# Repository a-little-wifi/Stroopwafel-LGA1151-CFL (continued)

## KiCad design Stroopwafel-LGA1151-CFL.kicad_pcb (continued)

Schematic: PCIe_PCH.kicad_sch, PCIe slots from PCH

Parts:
C69, C70, C71, C72, C73, C74, C75, C76, C77, C78, C79, C80, C81, C82, C83, C84, C85, C86, C87, C88, C89, C90, C91, C92, C93, C94, C95, C96, C97, C98, C99, C100, C101, C102, C103, C104, C105, C106, C107, C108: 0.22uF; C_0402_1005Metric
J6: Bus_M.2_Socket_M; m-key
J7: PCIe_x4_PCH_6; PCIe_x4_tht_open
J10: PCIe_x4_PCH_5; PCIe_x4_tht_open
J11: PCIe_x4_PCH_4; PCIe_x4_tht_open
J12: PCIe_x4_PCH_1; PCIe_x4_tht_open

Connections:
/PCIe_PCH/PCH_x4_1_PCIe_C_Tx0+: C101.2, J12.B14 (PETp0)
/PCIe_PCH/PCH_x4_1_PCIe_C_Tx0-: C102.2, J12.B15 (PETn0)
/PCIe_PCH/PCH_x4_1_PCIe_C_Tx1+: C103.2, J12.B19 (PETp1)
/PCIe_PCH/PCH_x4_1_PCIe_C_Tx1-: C104.2, J12.B20 (PETn1)
/PCIe_PCH/PCH_x4_1_PCIe_C_Tx2+: C105.2, J12.B23 (PETp2)
/PCIe_PCH/PCH_x4_1_PCIe_C_Tx2-: C106.2, J12.B24 (PETn2)
/PCIe_PCH/PCH_x4_1_PCIe_C_Tx3+: C107.2, J12.B27 (PETp3)
/PCIe_PCH/PCH_x4_1_PCIe_C_Tx3-: C108.2, J12.B28 (PETn3)
/PCIe_PCH/PCH_x4_4_PCIe_C_Tx0+: C93.2, J11.B14 (PETp0)
/PCIe_PCH/PCH_x4_4_PCIe_C_Tx0-: C94.2, J11.B15 (PETn0)
/PCIe_PCH/PCH_x4_4_PCIe_C_Tx1+: C95.2, J11.B19 (PETp1)
/PCIe_PCH/PCH_x4_4_PCIe_C_Tx1-: C96.2, J11.B20 (PETn1)
/PCIe_PCH/PCH_x4_4_PCIe_C_Tx2+: C97.2, J11.B23 (PETp2)
/PCIe_PCH/PCH_x4_4_PCIe_C_Tx2-: C98.2, J11.B24 (PETn2)
/PCIe_PCH/PCH_x4_4_PCIe_C_Tx3+: C99.2, J11.B27 (PETp3)
/PCIe_PCH/PCH_x4_4_PCIe_C_Tx3-: C100.2, J11.B28 (PETn3)
/PCIe_PCH/PCH_x4_5_PCIe_C_Tx0+: C85.2, J10.B14 (PETp0)
/PCIe_PCH/PCH_x4_5_PCIe_C_Tx0-: C86.2, J10.B15 (PETn0)
/PCIe_PCH/PCH_x4_5_PCIe_C_Tx1+: C87.2, J10.B19 (PETp1)
/PCIe_PCH/PCH_x4_5_PCIe_C_Tx1-: C88.2, J10.B20 (PETn1)
/PCIe_PCH/PCH_x4_5_PCIe_C_Tx2+: C89.2, J10.B23 (PETp2)
/PCIe_PCH/PCH_x4_5_PCIe_C_Tx2-: C90.2, J10.B24 (PETn2)
/PCIe_PCH/PCH_x4_5_PCIe_C_Tx3+: C91.2, J10.B27 (PETp3)
/PCIe_PCH/PCH_x4_5_PCIe_C_Tx3-: C92.2, J10.B28 (PETn3)
/PCIe_PCH/PCH_x4_6_PCIe_C_Tx0+: C77.2, J7.B14 (PETp0)
/PCIe_PCH/PCH_x4_6_PCIe_C_Tx0-: C78.2, J7.B15 (PETn0)
/PCIe_PCH/PCH_x4_6_PCIe_C_Tx1+: C79.2, J7.B19 (PETp1)
/PCIe_PCH/PCH_x4_6_PCIe_C_Tx1-: C80.2, J7.B20 (PETn1)
/PCIe_PCH/PCH_x4_6_PCIe_C_Tx2+: C81.2, J7.B23 (PETp2)
/PCIe_PCH/PCH_x4_6_PCIe_C_Tx2-: C82.2, J7.B24 (PETn2)
/PCIe_PCH/PCH_x4_6_PCIe_C_Tx3+: C83.2, J7.B27 (PETp3)
/PCIe_PCH/PCH_x4_6_PCIe_C_Tx3-: C84.2, J7.B28 (PETn3)
/PCIe_PCH/SSD0_PCIe_C_Tx1+: C71.2, J6.37 (PETp1)
/PCIe_PCH/SSD0_PCIe_C_Tx1-: C72.2, J6.35 (PETn1)
/PCIe_PCH/SSD0_PCIe_C_Tx2+: C73.2, J6.25 (PETp2)
/PCIe_PCH/SSD0_PCIe_C_Tx2-: C74.2, J6.23 (PETn2)
/PCIe_PCH/SSD0_PCIe_C_Tx3+: C75.2, J6.13 (PETp3)
/PCIe_PCH/SSD0_PCIe_C_Tx3-: C76.2, J6.11 (PETn3)
/PCIe_PCH/SSD0_SATA/PCIe_C_Tx0+: C69.2, J6.49 (PETp0/SATA-A+)
/PCIe_PCH/SSD0_SATA/PCIe_C_Tx0-: C70.2, J6.47 (PETn0/SATA-A-)
GND: J6.1 (GND), J6.3 (GND), J6.9 (GND), J6.15 (GND), J6.21 (GND), J6.27 (GND), J6.33 (GND), J6.39 (GND), J6.45 (GND), J6.51 (GND), J6.57 (GND), J6.71 (GND), J6.73 (GND), J6.75 (GND), J7.A1 (~PRSNT1), J10.A1 (~PRSNT1), J11.A1 (~PRSNT1), J12.A1 (~PRSNT1); also elsewhere on the board
unnamed: J7.A4 (GND), J7.A12 (GND), J7.A15 (GND), J7.A18 (GND), J7.A20 (GND), J7.A23 (GND), J7.A24 (GND), J7.A27 (GND), J7.A28 (GND), J7.A31 (GND)
unnamed: J7.B4 (GND), J7.B7 (GND), J7.B13 (GND), J7.B16 (GND), J7.B18 (GND), J7.B21 (GND), J7.B22 (GND), J7.B25 (GND), J7.B26 (GND), J7.B29 (GND), J7.B32 (GND)
unnamed: J10.A4 (GND), J10.A12 (GND), J10.A15 (GND), J10.A18 (GND), J10.A20 (GND), J10.A23 (GND), J10.A24 (GND), J10.A27 (GND), J10.A28 (GND), J10.A31 (GND)
unnamed: J10.B4 (GND), J10.B7 (GND), J10.B13 (GND), J10.B16 (GND), J10.B18 (GND), J10.B21 (GND), J10.B22 (GND), J10.B25 (GND), J10.B26 (GND), J10.B29 (GND), J10.B32 (GND)
unnamed: J11.A4 (GND), J11.A12 (GND), J11.A15 (GND), J11.A18 (GND), J11.A20 (GND), J11.A23 (GND), J11.A24 (GND), J11.A27 (GND), J11.A28 (GND), J11.A31 (GND)
unnamed: J11.B4 (GND), J11.B7 (GND), J11.B13 (GND), J11.B16 (GND), J11.B18 (GND), J11.B21 (GND), J11.B22 (GND), J11.B25 (GND), J11.B26 (GND), J11.B29 (GND), J11.B32 (GND)
unnamed: J12.A4 (GND), J12.A12 (GND), J12.A15 (GND), J12.A18 (GND), J12.A20 (GND), J12.A23 (GND), J12.A24 (GND), J12.A27 (GND), J12.A28 (GND), J12.A31 (GND)
unnamed: J12.B4 (GND), J12.B7 (GND), J12.B13 (GND), J12.B16 (GND), J12.B18 (GND), J12.B21 (GND), J12.B22 (GND), J12.B25 (GND), J12.B26 (GND), J12.B29 (GND), J12.B32 (GND)
PCH_x4_1_CLKREQ#: J12.B17 (~PRSNT2), J12.B31 (~PRSNT2); also elsewhere on the board
PCH_x4_1_PCIe_Rx0+: J12.A16 (PERp0); also elsewhere on the board
PCH_x4_1_PCIe_Rx0-: J12.A17 (PERn0); also elsewhere on the board
PCH_x4_1_PCIe_Rx1+: J12.A21 (PERp1); also elsewhere on the board
PCH_x4_1_PCIe_Rx1-: J12.A22 (PERn1); also elsewhere on the board
PCH_x4_1_PCIe_Rx2+: J12.A25 (PERp2); also elsewhere on the board
PCH_x4_1_PCIe_Rx2-: J12.A26 (PERn2); also elsewhere on the board
PCH_x4_1_PCIe_Rx3+: J12.A29 (PERp3); also elsewhere on the board
PCH_x4_1_PCIe_Rx3-: J12.A30 (PERn3); also elsewhere on the board
PCH_x4_1_PCIe_Tx0+: C101.1; also elsewhere on the board
PCH_x4_1_PCIe_Tx0-: C102.1; also elsewhere on the board
PCH_x4_1_PCIe_Tx1+: C103.1; also elsewhere on the board
PCH_x4_1_PCIe_Tx1-: C104.1; also elsewhere on the board
PCH_x4_1_PCIe_Tx2+: C105.1; also elsewhere on the board
PCH_x4_1_PCIe_Tx2-: C106.1; also elsewhere on the board
PCH_x4_1_PCIe_Tx3+: C107.1; also elsewhere on the board
PCH_x4_1_PCIe_Tx3-: C108.1; also elsewhere on the board
PCH_x4_1_Refclk+: J12.A13 (REFCLK+); also elsewhere on the board
PCH_x4_1_Refclk-: J12.A14 (REFCLK-); also elsewhere on the board
PCH_x4_4_CLKREQ#: J11.B17 (~PRSNT2), J11.B31 (~PRSNT2); also elsewhere on the board
PCH_x4_4_PCIe_Rx0+: J11.A16 (PERp0); also elsewhere on the board
PCH_x4_4_PCIe_Rx0-: J11.A17 (PERn0); also elsewhere on the board
PCH_x4_4_PCIe_Rx1+: J11.A21 (PERp1); also elsewhere on the board
PCH_x4_4_PCIe_Rx1-: J11.A22 (PERn1); also elsewhere on the board
PCH_x4_4_PCIe_Rx2+: J11.A25 (PERp2); also elsewhere on the board
PCH_x4_4_PCIe_Rx2-: J11.A26 (PERn2); also elsewhere on the board
PCH_x4_4_PCIe_Rx3+: J11.A29 (PERp3); also elsewhere on the board
PCH_x4_4_PCIe_Rx3-: J11.A30 (PERn3); also elsewhere on the board
PCH_x4_4_PCIe_Tx0+: C93.1; also elsewhere on the board
PCH_x4_4_PCIe_Tx0-: C94.1; also elsewhere on the board
PCH_x4_4_PCIe_Tx1+: C95.1; also elsewhere on the board
PCH_x4_4_PCIe_Tx1-: C96.1; also elsewhere on the board
PCH_x4_4_PCIe_Tx2+: C97.1; also elsewhere on the board
PCH_x4_4_PCIe_Tx2-: C98.1; also elsewhere on the board
PCH_x4_4_PCIe_Tx3+: C99.1; also elsewhere on the board
PCH_x4_4_PCIe_Tx3-: C100.1; also elsewhere on the board
PCH_x4_4_Refclk+: J11.A13 (REFCLK+); also elsewhere on the board
PCH_x4_4_Refclk-: J11.A14 (REFCLK-); also elsewhere on the board
PCH_x4_5_CLKREQ#: J10.B17 (~PRSNT2), J10.B31 (~PRSNT2); also elsewhere on the board
PCH_x4_5_PCIe_Rx0+: J10.A16 (PERp0); also elsewhere on the board
PCH_x4_5_PCIe_Rx0-: J10.A17 (PERn0); also elsewhere on the board
PCH_x4_5_PCIe_Rx1+: J10.A21 (PERp1); also elsewhere on the board
PCH_x4_5_PCIe_Rx1-: J10.A22 (PERn1); also elsewhere on the board
PCH_x4_5_PCIe_Rx2+: J10.A25 (PERp2); also elsewhere on the board
PCH_x4_5_PCIe_Rx2-: J10.A26 (PERn2); also elsewhere on the board
PCH_x4_5_PCIe_Rx3+: J10.A29 (PERp3); also elsewhere on the board
PCH_x4_5_PCIe_Rx3-: J10.A30 (PERn3); also elsewhere on the board
PCH_x4_5_PCIe_Tx0+: C85.1; also elsewhere on the board
PCH_x4_5_PCIe_Tx0-: C86.1; also elsewhere on the board
PCH_x4_5_PCIe_Tx1+: C87.1; also elsewhere on the board
PCH_x4_5_PCIe_Tx1-: C88.1; also elsewhere on the board
PCH_x4_5_PCIe_Tx2+: C89.1; also elsewhere on the board
PCH_x4_5_PCIe_Tx2-: C90.1; also elsewhere on the board
PCH_x4_5_PCIe_Tx3+: C91.1; also elsewhere on the board
PCH_x4_5_PCIe_Tx3-: C92.1; also elsewhere on the board
PCH_x4_5_Refclk+: J10.A13 (REFCLK+); also elsewhere on the board
PCH_x4_5_Refclk-: J10.A14 (REFCLK-); also elsewhere on the board
PCH_x4_6_CLKREQ#: J7.B17 (~PRSNT2), J7.B31 (~PRSNT2); also elsewhere on the board
PCH_x4_6_PCIe_Rx0+: J7.A16 (PERp0); also elsewhere on the board
PCH_x4_6_PCIe_Rx0-: J7.A17 (PERn0); also elsewhere on the board
PCH_x4_6_PCIe_Rx1+: J7.A21 (PERp1); also elsewhere on the board
PCH_x4_6_PCIe_Rx1-: J7.A22 (PERn1); also elsewhere on the board
PCH_x4_6_PCIe_Rx2+: J7.A25 (PERp2); also elsewhere on the board
PCH_x4_6_PCIe_Rx2-: J7.A26 (PERn2); also elsewhere on the board
PCH_x4_6_PCIe_Rx3+: J7.A29 (PERp3); also elsewhere on the board
PCH_x4_6_PCIe_Rx3-: J7.A30 (PERn3); also elsewhere on the board
PCH_x4_6_PCIe_Tx0+: C77.1; also elsewhere on the board
PCH_x4_6_PCIe_Tx0-: C78.1; also elsewhere on the board
PCH_x4_6_PCIe_Tx1+: C79.1; also elsewhere on the board
PCH_x4_6_PCIe_Tx1-: C80.1; also elsewhere on the board
PCH_x4_6_PCIe_Tx2+: C81.1; also elsewhere on the board
PCH_x4_6_PCIe_Tx2-: C82.1; also elsewhere on the board
PCH_x4_6_PCIe_Tx3+: C83.1; also elsewhere on the board
PCH_x4_6_PCIe_Tx3-: C84.1; also elsewhere on the board
PCH_x4_6_Refclk+: J7.A13 (REFCLK+); also elsewhere on the board
PCH_x4_6_Refclk-: J7.A14 (REFCLK-); also elsewhere on the board
SSD0_CLKREQ#: J6.52 (~CLKREQ); also elsewhere on the board
SSD0_PCIe_Rx1+: J6.31 (PERp1); also elsewhere on the board
SSD0_PCIe_Rx1-: J6.29 (PERn1); also elsewhere on the board
SSD0_PCIe_Rx2+: J6.19 (PERp2); also elsewhere on the board
SSD0_PCIe_Rx2-: J6.17 (PERn2); also elsewhere on the board
SSD0_PCIe_Rx3+: J6.7 (PERp3); also elsewhere on the board
SSD0_PCIe_Rx3-: J6.5 (PERn3); also elsewhere on the board
SSD0_PCIe_Tx1+: C71.1; also elsewhere on the board
SSD0_PCIe_Tx1-: C72.1; also elsewhere on the board
SSD0_PCIe_Tx2+: C73.1; also elsewhere on the board
SSD0_PCIe_Tx2-: C74.1; also elsewhere on the board
SSD0_PCIe_Tx3+: C75.1; also elsewhere on the board
SSD0_PCIe_Tx3-: C76.1; also elsewhere on the board
SSD0_Refclk+: J6.55 (REFCLKp); also elsewhere on the board
SSD0_Refclk-: J6.53 (REFCLKn); also elsewhere on the board
SSD0_SATA/PCIe_Rx0+: J6.41 (PERn0/SATA-B+); also elsewhere on the board
SSD0_SATA/PCIe_Rx0-: J6.43 (PERp0/SATA-B-); also elsewhere on the board
SSD0_SATA/PCIe_Tx0+: C69.1; also elsewhere on the board
SSD0_SATA/PCIe_Tx0-: C70.1; also elsewhere on the board
temp_3.3V: J6.2 (3.3V), J6.4 (3.3V), J6.12 (3.3V), J6.14 (3.3V), J6.16 (3.3V), J6.18 (3.3V), J6.70 (3.3V), J6.72 (3.3V), J6.74 (3.3V), J7.A9 (+3.3V), J7.A10 (+3.3V), J7.B8 (+3.3V), J10.A9 (+3.3V), J10.A10 (+3.3V), J10.B8 (+3.3V), J11.A9 (+3.3V), J11.A10 (+3.3V), J11.B8 (+3.3V), J12.A9 (+3.3V), J12.A10 (+3.3V), J12.B8 (+3.3V); also elsewhere on the board
temp_12V: J7.A2 (+12V), J7.A3 (+12V), J7.B1 (+12V), J7.B2 (+12V), J7.B3 (+12V), J10.A2 (+12V), J10.A3 (+12V), J10.B1 (+12V), J10.B2 (+12V), J10.B3 (+12V), J11.A2 (+12V), J11.A3 (+12V), J11.B1 (+12V), J11.B2 (+12V), J11.B3 (+12V), J12.A2 (+12V), J12.A3 (+12V), J12.B1 (+12V), J12.B2 (+12V), J12.B3 (+12V); also elsewhere on the board

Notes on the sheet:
polarity inverted for sata support

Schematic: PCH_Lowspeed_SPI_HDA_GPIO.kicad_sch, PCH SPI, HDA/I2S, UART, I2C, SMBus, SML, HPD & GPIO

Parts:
R1, R3: 30Ω; R_0402_1005Metric
R2: 20Ω; R_0402_1005Metric
R33: 33.2Ω; R_0402_1005Metric
UPCH1: Intel Cannon Point 300-Series Platform Controller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; CNP-H_BGA_874P-T

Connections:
CPU_DisplayAudio_CLK: R3.1; also elsewhere on the board
CPU_DisplayAudio_SDI: R1.1; also elsewhere on the board
CPU_DisplayAudio_SDO: R2.1; also elsewhere on the board
CPU_PWRGD: UPCH1.AE3 (CPUPWRGD); also elsewhere on the board
unnamed: R3.2, UPCH1.AM3 (HDACPU_SCLK)
unnamed: R2.2, UPCH1.AN3 (HDACPU_SDI)
unnamed: R1.2, UPCH1.AM2 (HDACPU_SDO)
unnamed: R33.1, UPCH1.AK3 (TRIGGER_OUT)
TRIG_CPU_TO_PCH: UPCH1.AK2 (TRIGGER_IN); also elsewhere on the board
TRIG_PCH_TO_CPU: R33.2; also elsewhere on the board
iGPU_DDI1_SCL: UPCH1.AL13 (GPP_I5/DDPB_CTRLCLK); also elsewhere on the board
iGPU_DDI1_SDA: UPCH1.AR8 (GPP_I6/DDPB_CTRLDATA); also elsewhere on the board
iGPU_DDI2_SCL: UPCH1.AN13 (GPP_I7/DDPC_CTRLCLK)
iGPU_DDI2_SDA: UPCH1.AL10 (GPP_I8/DDPC_CTRLDATA)
iGPU_DDI3_SCL: UPCH1.AL9 (GPP_I9/DDPD_CTRLCLK)
iGPU_DDI3_SDA: UPCH1.AR3 (GPP_I10/DDPD_CTRLDATA)

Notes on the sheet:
place the resistor physically close to the OUT pin on each end?
CPU SDI to PCH SDO, SDO to SDI

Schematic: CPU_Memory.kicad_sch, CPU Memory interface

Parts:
JCPU1: Intel 8th/9th Generation Coffee-Lake LGA1151 CPU; LGA-1151_L47.1-W42.5-P0.91_PE115127-4041-01H

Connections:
DDR4_CH0_A0: JCPU1.AW15 (DDR0_MA_0); also elsewhere on the board
DDR4_CH0_A1: JCPU1.AU18 (DDR0_MA_1); also elsewhere on the board
DDR4_CH0_A2: JCPU1.AU17 (DDR0_MA_2); also elsewhere on the board
DDR4_CH0_A3: JCPU1.AV19 (DDR0_MA_3); also elsewhere on the board
DDR4_CH0_A4: JCPU1.AT19 (DDR0_MA_4); also elsewhere on the board
DDR4_CH0_A5: JCPU1.AU20 (DDR0_MA_5); also elsewhere on the board
DDR4_CH0_A6: JCPU1.AV20 (DDR0_MA_6); also elsewhere on the board
DDR4_CH0_A7: JCPU1.AU21 (DDR0_MA_7); also elsewhere on the board
DDR4_CH0_A8: JCPU1.AT20 (DDR0_MA_8); also elsewhere on the board
DDR4_CH0_A9: JCPU1.AT22 (DDR0_MA_9); also elsewhere on the board
DDR4_CH0_A10: JCPU1.AY14 (DDR0_MA_10); also elsewhere on the board
DDR4_CH0_A11: JCPU1.AU22 (DDR0_MA_11); also elsewhere on the board
DDR4_CH0_A12: JCPU1.AV22 (DDR0_MA_12); also elsewhere on the board
DDR4_CH0_A13: JCPU1.AV12 (DDR0_MA_13); also elsewhere on the board
DDR4_CH0_A14_WE#: JCPU1.AV14 (DDR0_MA_14); also elsewhere on the board
DDR4_CH0_A15_CAS#: JCPU1.AY11 (DDR0_MA_15); also elsewhere on the board
DDR4_CH0_A16_RAS#: JCPU1.AW13 (DDR0_MA_16); also elsewhere on the board
DDR4_CH0_ACT#: JCPU1.AU24 (DDR0_ACT#); also elsewhere on the board
DDR4_CH0_Alert#: JCPU1.AT23 (DDR0_ALERT#); also elsewhere on the board
DDR4_CH0_BA0: JCPU1.AY13 (DDR0_BA_0); also elsewhere on the board
DDR4_CH0_BA1: JCPU1.AV15 (DDR0_BA_1); also elsewhere on the board
DDR4_CH0_BG0: JCPU1.AW23 (DDR0_BG_0); also elsewhere on the board
DDR4_CH0_BG1: JCPU1.AV23 (DDR0_BG_1); also elsewhere on the board
DDR4_CH0_CKE0: JCPU1.AY24 (DDR0_CKE_0); also elsewhere on the board
DDR4_CH0_CKE1: JCPU1.AW24 (DDR0_CKE_1); also elsewhere on the board
DDR4_CH0_CLK0+: JCPU1.AW18 (DDR0_CKP_0); also elsewhere on the board
DDR4_CH0_CLK0-: JCPU1.AV18 (DDR0_CKN_0); also elsewhere on the board
DDR4_CH0_CLK1+: JCPU1.AW17 (DDR0_CKP_1); also elsewhere on the board
DDR4_CH0_CLK1-: JCPU1.AY17 (DDR0_CKN_1); also elsewhere on the board
DDR4_CH0_CS0#: JCPU1.AW12 (DDR0_CS#_0); also elsewhere on the board
DDR4_CH0_CS1#: JCPU1.AU11 (DDR0_CS#_1); also elsewhere on the board
DDR4_CH0_DQ0: JCPU1.AE38 (DDR0_DQ_0/DDR0_DQ_0); also elsewhere on the board
DDR4_CH0_DQ1: JCPU1.AE37 (DDR0_DQ_1/DDR0_DQ_1); also elsewhere on the board
DDR4_CH0_DQ2: JCPU1.AG38 (DDR0_DQ_2/DDR0_DQ_2); also elsewhere on the board
DDR4_CH0_DQ3: JCPU1.AG37 (DDR0_DQ_3/DDR0_DQ_3); also elsewhere on the board
DDR4_CH0_DQ4: JCPU1.AE39 (DDR0_DQ_4/DDR0_DQ_4); also elsewhere on the board
DDR4_CH0_DQ5: JCPU1.AE40 (DDR0_DQ_5/DDR0_DQ_5); also elsewhere on the board
DDR4_CH0_DQ6: JCPU1.AG39 (DDR0_DQ_6/DDR0_DQ_6); also elsewhere on the board
DDR4_CH0_DQ7: JCPU1.AG40 (DDR0_DQ_7/DDR0_DQ_7); also elsewhere on the board
DDR4_CH0_DQ8: JCPU1.AJ38 (DDR0_DQ_8/DDR0_DQ_8); also elsewhere on the board
DDR4_CH0_DQ9: JCPU1.AJ37 (DDR0_DQ_9/DDR0_DQ_9); also elsewhere on the board
DDR4_CH0_DQ10: JCPU1.AL38 (DDR0_DQ_10/DDR0_DQ_10); also elsewhere on the board
DDR4_CH0_DQ11: JCPU1.AL37 (DDR0_DQ_11/DDR0_DQ_11); also elsewhere on the board
DDR4_CH0_DQ12: JCPU1.AJ40 (DDR0_DQ_12/DDR0_DQ_12); also elsewhere on the board
DDR4_CH0_DQ13: JCPU1.AJ39 (DDR0_DQ_13/DDR0_DQ_13); also elsewhere on the board
DDR4_CH0_DQ14: JCPU1.AL39 (DDR0_DQ_14/DDR0_DQ_14); also elsewhere on the board
DDR4_CH0_DQ15: JCPU1.AL40 (DDR0_DQ_15/DDR0_DQ_15); also elsewhere on the board
DDR4_CH0_DQ16: JCPU1.AN38 (DDR0_DQ_16/DDR0_DQ_32); also elsewhere on the board
DDR4_CH0_DQ17: JCPU1.AN40 (DDR0_DQ_17/DDR0_DQ_33); also elsewhere on the board
DDR4_CH0_DQ18: JCPU1.AR38 (DDR0_DQ_18/DDR0_DQ_34); also elsewhere on the board
DDR4_CH0_DQ19: JCPU1.AR37 (DDR0_DQ_19/DDR0_DQ_35); also elsewhere on the board
DDR4_CH0_DQ20: JCPU1.AN39 (DDR0_DQ_20/DDR0_DQ_36); also elsewhere on the board
DDR4_CH0_DQ21: JCPU1.AN37 (DDR0_DQ_21/DDR0_DQ_37); also elsewhere on the board
DDR4_CH0_DQ22: JCPU1.AR39 (DDR0_DQ_22/DDR0_DQ_38); also elsewhere on the board
DDR4_CH0_DQ23: JCPU1.AR40 (DDR0_DQ_23/DDR0_DQ_39); also elsewhere on the board
DDR4_CH0_DQ24: JCPU1.AW37 (DDR0_DQ_24/DDR0_DQ_40); also elsewhere on the board
DDR4_CH0_DQ25: JCPU1.AU38 (DDR0_DQ_25/DDR0_DQ_41); also elsewhere on the board
DDR4_CH0_DQ26: JCPU1.AV35 (DDR0_DQ_26/DDR0_DQ_42); also elsewhere on the board
DDR4_CH0_DQ27: JCPU1.AW35 (DDR0_DQ_27/DDR0_DQ_43); also elsewhere on the board
DDR4_CH0_DQ28: JCPU1.AU37 (DDR0_DQ_28/DDR0_DQ_44); also elsewhere on the board
DDR4_CH0_DQ29: JCPU1.AV37 (DDR0_DQ_29/DDR0_DQ_45); also elsewhere on the board
DDR4_CH0_DQ30: JCPU1.AT35 (DDR0_DQ_30/DDR0_DQ_46); also elsewhere on the board
DDR4_CH0_DQ31: JCPU1.AU35 (DDR0_DQ_31/DDR0_DQ_47); also elsewhere on the board
DDR4_CH0_DQ32: JCPU1.AY8 (DDR0_DQ_32/DDR1_DQ_0); also elsewhere on the board
DDR4_CH0_DQ33: JCPU1.AW8 (DDR0_DQ_33/DDR1_DQ_1); also elsewhere on the board
DDR4_CH0_DQ34: JCPU1.AV6 (DDR0_DQ_34/DDR1_DQ_2); also elsewhere on the board
DDR4_CH0_DQ35: JCPU1.AU6 (DDR0_DQ_35/DDR1_DQ_3); also elsewhere on the board
DDR4_CH0_DQ36: JCPU1.AU8 (DDR0_DQ_36/DDR1_DQ_4); also elsewhere on the board
DDR4_CH0_DQ37: JCPU1.AV8 (DDR0_DQ_37/DDR1_DQ_5); also elsewhere on the board
DDR4_CH0_DQ38: JCPU1.AW6 (DDR0_DQ_38/DDR1_DQ_6); also elsewhere on the board
DDR4_CH0_DQ39: JCPU1.AY6 (DDR0_DQ_39/DDR1_DQ_7); also elsewhere on the board
DDR4_CH0_DQ40: JCPU1.AY4 (DDR0_DQ_40/DDR1_DQ_8); also elsewhere on the board
DDR4_CH0_DQ41: JCPU1.AV4 (DDR0_DQ_41/DDR1_DQ_9); also elsewhere on the board
DDR4_CH0_DQ42: JCPU1.AT1 (DDR0_DQ_42/DDR1_DQ_10); also elsewhere on the board
DDR4_CH0_DQ43: JCPU1.AT2 (DDR0_DQ_43/DDR1_DQ_11); also elsewhere on the board
DDR4_CH0_DQ44: JCPU1.AV3 (DDR0_DQ_44/DDR1_DQ_12); also elsewhere on the board
DDR4_CH0_DQ45: JCPU1.AW4 (DDR0_DQ_45/DDR1_DQ_13); also elsewhere on the board
DDR4_CH0_DQ46: JCPU1.AT4 (DDR0_DQ_46/DDR1_DQ_14); also elsewhere on the board
DDR4_CH0_DQ47: JCPU1.AT3 (DDR0_DQ_47/DDR1_DQ_15); also elsewhere on the board
DDR4_CH0_DQ48: JCPU1.AP2 (DDR0_DQ_48/DDR1_DQ_32); also elsewhere on the board
DDR4_CH0_DQ49: JCPU1.AM4 (DDR0_DQ_49/DDR1_DQ_33); also elsewhere on the board
DDR4_CH0_DQ50: JCPU1.AP3 (DDR0_DQ_50/DDR1_DQ_34); also elsewhere on the board
DDR4_CH0_DQ51: JCPU1.AM3 (DDR0_DQ_51/DDR1_DQ_35); also elsewhere on the board
DDR4_CH0_DQ52: JCPU1.AP4 (DDR0_DQ_52/DDR1_DQ_36); also elsewhere on the board
DDR4_CH0_DQ53: JCPU1.AM2 (DDR0_DQ_53/DDR1_DQ_37); also elsewhere on the board
DDR4_CH0_DQ54: JCPU1.AP1 (DDR0_DQ_54/DDR1_DQ_38); also elsewhere on the board
DDR4_CH0_DQ55: JCPU1.AM1 (DDR0_DQ_55/DDR1_DQ_39); also elsewhere on the board
DDR4_CH0_DQ56: JCPU1.AK3 (DDR0_DQ_56/DDR1_DQ_40); also elsewhere on the board
DDR4_CH0_DQ57: JCPU1.AH1 (DDR0_DQ_57/DDR1_DQ_41); also elsewhere on the board
DDR4_CH0_DQ58: JCPU1.AK4 (DDR0_DQ_58/DDR1_DQ_42); also elsewhere on the board
DDR4_CH0_DQ59: JCPU1.AH2 (DDR0_DQ_59/DDR1_DQ_43); also elsewhere on the board
DDR4_CH0_DQ60: JCPU1.AH4 (DDR0_DQ_60/DDR1_DQ_44); also elsewhere on the board
DDR4_CH0_DQ61: JCPU1.AK2 (DDR0_DQ_61/DDR1_DQ_45); also elsewhere on the board
DDR4_CH0_DQ62: JCPU1.AH3 (DDR0_DQ_62/DDR1_DQ_46); also elsewhere on the board
DDR4_CH0_DQ63: JCPU1.AK1 (DDR0_DQ_63/DDR1_DQ_47); also elsewhere on the board
DDR4_CH0_DQS0+: JCPU1.AF38 (DDR0_DQSP_0/DDR0_DQSP_0); also elsewhere on the board
DDR4_CH0_DQS0-: JCPU1.AF39 (DDR0_DQSN_0/DDR0_DQSN_0); also elsewhere on the board
DDR4_CH0_DQS1+: JCPU1.AK38 (DDR0_DQSP_1/DDR0_DQSP_1); also elsewhere on the board
DDR4_CH0_DQS1-: JCPU1.AK39 (DDR0_DQSN_1/DDR0_DQSN_1); also elsewhere on the board
DDR4_CH0_DQS2+: JCPU1.AP38 (DDR0_DQSP_2/DDR0_DQSP_4); also elsewhere on the board
DDR4_CH0_DQS2-: JCPU1.AP39 (DDR0_DQSN_2/DDR0_DQSN_4); also elsewhere on the board
DDR4_CH0_DQS3+: JCPU1.AV36 (DDR0_DQSP_3/DDR0_DQSP_5); also elsewhere on the board
DDR4_CH0_DQS3-: JCPU1.AU36 (DDR0_DQSN_3/DDR0_DQSN_5); also elsewhere on the board
DDR4_CH0_DQS4+: JCPU1.AV7 (DDR0_DQSP_4/DDR1_DQSP_0); also elsewhere on the board
DDR4_CH0_DQS4-: JCPU1.AW7 (DDR0_DQSN_4/DDR1_DQSN_0); also elsewhere on the board
DDR4_CH0_DQS5+: JCPU1.AU2 (DDR0_DQSP_5/DDR1_DQSP_1); also elsewhere on the board
DDR4_CH0_DQS5-: JCPU1.AU3 (DDR0_DQSN_5/DDR1_DQSN_1); also elsewhere on the board
DDR4_CH0_DQS6+: JCPU1.AN2 (DDR0_DQSP_6/DDR1_DQSP_4); also elsewhere on the board
DDR4_CH0_DQS6-: JCPU1.AN3 (DDR0_DQSN_6/DDR1_DQSN_4); also elsewhere on the board
DDR4_CH0_DQS7+: JCPU1.AJ2 (DDR0_DQSP_7/DDR1_DQSP_5); also elsewhere on the board
DDR4_CH0_DQS7-: JCPU1.AJ3 (DDR0_DQSN_7/DDR1_DQSN_5); also elsewhere on the board
DDR4_CH0_DQS8+: JCPU1.AV32 (DDR0_DQSP_8/DDR0_DQSP_8); also elsewhere on the board
DDR4_CH0_DQS8-: JCPU1.AU32 (DDR0_DQSN_8/DDR0_DQSN_8); also elsewhere on the board
DDR4_CH0_ECC0: JCPU1.AU33 (DDR0_ECC_0); also elsewhere on the board
DDR4_CH0_ECC1: JCPU1.AT33 (DDR0_ECC_1); also elsewhere on the board
DDR4_CH0_ECC2: JCPU1.AW33 (DDR0_ECC_2); also elsewhere on the board
DDR4_CH0_ECC3: JCPU1.AV31 (DDR0_ECC_3); also elsewhere on the board
DDR4_CH0_ECC4: JCPU1.AU31 (DDR0_ECC_4); also elsewhere on the board
DDR4_CH0_ECC5: JCPU1.AV33 (DDR0_ECC_5); also elsewhere on the board
DDR4_CH0_ECC6: JCPU1.AW31 (DDR0_ECC_6); also elsewhere on the board
DDR4_CH0_ECC7: JCPU1.AY31 (DDR0_ECC_7); also elsewhere on the board
DDR4_CH0_ODT0: JCPU1.AW11 (DDR0_ODT_0); also elsewhere on the board
DDR4_CH0_ODT1: JCPU1.AU14 (DDR0_ODT_1); also elsewhere on the board
DDR4_CH0_Parity: JCPU1.AY15 (DDR0_PAR); also elsewhere on the board
DDR4_CH1_A0: JCPU1.AL19 (DDR1_MA_0); also elsewhere on the board
DDR4_CH1_A1: JCPU1.AL22 (DDR1_MA_1); also elsewhere on the board
DDR4_CH1_A2: JCPU1.AM22 (DDR1_MA_2); also elsewhere on the board
DDR4_CH1_A3: JCPU1.AM23 (DDR1_MA_3); also elsewhere on the board
DDR4_CH1_A4: JCPU1.AP23 (DDR1_MA_4); also elsewhere on the board
DDR4_CH1_A5: JCPU1.AL23 (DDR1_MA_5); also elsewhere on the board
DDR4_CH1_A6: JCPU1.AW26 (DDR1_MA_6); also elsewhere on the board
DDR4_CH1_A7: JCPU1.AY26 (DDR1_MA_7); also elsewhere on the board
DDR4_CH1_A8: JCPU1.AU26 (DDR1_MA_8); also elsewhere on the board
DDR4_CH1_A9: JCPU1.AW27 (DDR1_MA_9); also elsewhere on the board
DDR4_CH1_A10: JCPU1.AP18 (DDR1_MA_10); also elsewhere on the board
DDR4_CH1_A11: JCPU1.AU27 (DDR1_MA_11); also elsewhere on the board
DDR4_CH1_A12: JCPU1.AV27 (DDR1_MA_12); also elsewhere on the board
DDR4_CH1_A13: JCPU1.AR15 (DDR1_MA_13); also elsewhere on the board
DDR4_CH1_A14_WE#: JCPU1.AL17 (DDR1_MA_14); also elsewhere on the board
DDR4_CH1_A15_CAS#: JCPU1.AP16 (DDR1_MA_15); also elsewhere on the board
DDR4_CH1_A16_RAS#: JCPU1.AN18 (DDR1_MA_16); also elsewhere on the board
DDR4_CH1_ACT#: JCPU1.AU28 (DDR1_ACT#); also elsewhere on the board
DDR4_CH1_Alert#: JCPU1.AY25 (DDR1_ALERT#); also elsewhere on the board
DDR4_CH1_BA0: JCPU1.AL18 (DDR1_BA_0); also elsewhere on the board
DDR4_CH1_BA1: JCPU1.AM18 (DDR1_BA_1); also elsewhere on the board
DDR4_CH1_BG0: JCPU1.AW28 (DDR1_BG_0); also elsewhere on the board
DDR4_CH1_BG1: JCPU1.AY28 (DDR1_BG_1); also elsewhere on the board
DDR4_CH1_CKE0: JCPU1.AY29 (DDR1_CKE_0); also elsewhere on the board
DDR4_CH1_CKE1: JCPU1.AV29 (DDR1_CKE_1); also elsewhere on the board
DDR4_CH1_CLK0+: JCPU1.AM20 (DDR1_CKP_0); also elsewhere on the board
DDR4_CH1_CLK0-: JCPU1.AM21 (DDR1_CKN_0); also elsewhere on the board
DDR4_CH1_CLK1+: JCPU1.AP22 (DDR1_CKP_1); also elsewhere on the board
DDR4_CH1_CLK1-: JCPU1.AP21 (DDR1_CKN_1); also elsewhere on the board
DDR4_CH1_CS0#: JCPU1.AP17 (DDR1_CS#_0); also elsewhere on the board
DDR4_CH1_CS1#: JCPU1.AN15 (DDR1_CS#_1); also elsewhere on the board
DDR4_CH1_DQ0: JCPU1.AD34 (DDR1_DQ_0/DDR0_DQ_16); also elsewhere on the board
DDR4_CH1_DQ1: JCPU1.AD35 (DDR1_DQ_1/DDR0_DQ_17); also elsewhere on the board
DDR4_CH1_DQ2: JCPU1.AG35 (DDR1_DQ_2/DDR0_DQ_18); also elsewhere on the board
DDR4_CH1_DQ3: JCPU1.AH35 (DDR1_DQ_3/DDR0_DQ_19); also elsewhere on the board
DDR4_CH1_DQ4: JCPU1.AE35 (DDR1_DQ_4/DDR0_DQ_20); also elsewhere on the board
DDR4_CH1_DQ5: JCPU1.AE34 (DDR1_DQ_5/DDR0_DQ_21); also elsewhere on the board
DDR4_CH1_DQ6: JCPU1.AG34 (DDR1_DQ_6/DDR0_DQ_22); also elsewhere on the board
DDR4_CH1_DQ7: JCPU1.AH34 (DDR1_DQ_7/DDR0_DQ_23); also elsewhere on the board
DDR4_CH1_DQ8: JCPU1.AK35 (DDR1_DQ_8/DDR0_DQ_24); also elsewhere on the board
DDR4_CH1_DQ9: JCPU1.AL35 (DDR1_DQ_9/DDR0_DQ_25); also elsewhere on the board
DDR4_CH1_DQ10: JCPU1.AK32 (DDR1_DQ_10/DDR0_DQ_26); also elsewhere on the board
DDR4_CH1_DQ11: JCPU1.AL32 (DDR1_DQ_11/DDR0_DQ_27); also elsewhere on the board
DDR4_CH1_DQ12: JCPU1.AK34 (DDR1_DQ_12/DDR0_DQ_28); also elsewhere on the board
DDR4_CH1_DQ13: JCPU1.AL34 (DDR1_DQ_13/DDR0_DQ_29); also elsewhere on the board
DDR4_CH1_DQ14: JCPU1.AK31 (DDR1_DQ_14/DDR0_DQ_30); also elsewhere on the board
DDR4_CH1_DQ15: JCPU1.AL31 (DDR1_DQ_15/DDR0_DQ_31); also elsewhere on the board
DDR4_CH1_DQ16: JCPU1.AP35 (DDR1_DQ_16/DDR0_DQ_48); also elsewhere on the board
DDR4_CH1_DQ17: JCPU1.AN35 (DDR1_DQ_17/DDR0_DQ_49); also elsewhere on the board
DDR4_CH1_DQ18: JCPU1.AN32 (DDR1_DQ_18/DDR0_DQ_50); also elsewhere on the board
DDR4_CH1_DQ19: JCPU1.AP32 (DDR1_DQ_19/DDR0_DQ_51); also elsewhere on the board
DDR4_CH1_DQ20: JCPU1.AN34 (DDR1_DQ_20/DDR0_DQ_52); also elsewhere on the board
DDR4_CH1_DQ21: JCPU1.AP34 (DDR1_DQ_21/DDR0_DQ_53); also elsewhere on the board
DDR4_CH1_DQ22: JCPU1.AN31 (DDR1_DQ_22/DDR0_DQ_54); also elsewhere on the board
DDR4_CH1_DQ23: JCPU1.AP31 (DDR1_DQ_23/DDR0_DQ_55); also elsewhere on the board
DDR4_CH1_DQ24: JCPU1.AL29 (DDR1_DQ_24/DDR0_DQ_56); also elsewhere on the board
DDR4_CH1_DQ25: JCPU1.AM29 (DDR1_DQ_25/DDR0_DQ_57); also elsewhere on the board
DDR4_CH1_DQ26: JCPU1.AP29 (DDR1_DQ_26/DDR0_DQ_58); also elsewhere on the board
DDR4_CH1_DQ27: JCPU1.AR29 (DDR1_DQ_27/DDR0_DQ_59); also elsewhere on the board
DDR4_CH1_DQ28: JCPU1.AM28 (DDR1_DQ_28/DDR0_DQ_60); also elsewhere on the board
DDR4_CH1_DQ29: JCPU1.AL28 (DDR1_DQ_29/DDR0_DQ_61); also elsewhere on the board
DDR4_CH1_DQ30: JCPU1.AR28 (DDR1_DQ_30/DDR0_DQ_62); also elsewhere on the board
DDR4_CH1_DQ31: JCPU1.AP28 (DDR1_DQ_31/DDR0_DQ_63); also elsewhere on the board
DDR4_CH1_DQ32: JCPU1.AR12 (DDR1_DQ_32/DDR1_DQ_16); also elsewhere on the board
DDR4_CH1_DQ33: JCPU1.AP12 (DDR1_DQ_33/DDR1_DQ_17); also elsewhere on the board
DDR4_CH1_DQ34: JCPU1.AM13 (DDR1_DQ_34/DDR1_DQ_18); also elsewhere on the board
DDR4_CH1_DQ35: JCPU1.AL13 (DDR1_DQ_35/DDR1_DQ_19); also elsewhere on the board
DDR4_CH1_DQ36: JCPU1.AR13 (DDR1_DQ_36/DDR1_DQ_20); also elsewhere on the board
DDR4_CH1_DQ37: JCPU1.AP13 (DDR1_DQ_37/DDR1_DQ_21); also elsewhere on the board
DDR4_CH1_DQ38: JCPU1.AM12 (DDR1_DQ_38/DDR1_DQ_22); also elsewhere on the board
DDR4_CH1_DQ39: JCPU1.AL12 (DDR1_DQ_39/DDR1_DQ_23); also elsewhere on the board
DDR4_CH1_DQ40: JCPU1.AP10 (DDR1_DQ_40/DDR1_DQ_24); also elsewhere on the board
DDR4_CH1_DQ41: JCPU1.AR10 (DDR1_DQ_41/DDR1_DQ_25); also elsewhere on the board
DDR4_CH1_DQ42: JCPU1.AR7 (DDR1_DQ_42/DDR1_DQ_26); also elsewhere on the board
DDR4_CH1_DQ43: JCPU1.AP7 (DDR1_DQ_43/DDR1_DQ_27); also elsewhere on the board
DDR4_CH1_DQ44: JCPU1.AR9 (DDR1_DQ_44/DDR1_DQ_28); also elsewhere on the board
DDR4_CH1_DQ45: JCPU1.AP9 (DDR1_DQ_45/DDR1_DQ_29); also elsewhere on the board
DDR4_CH1_DQ46: JCPU1.AR6 (DDR1_DQ_46/DDR1_DQ_30); also elsewhere on the board
DDR4_CH1_DQ47: JCPU1.AP6 (DDR1_DQ_47/DDR1_DQ_31); also elsewhere on the board
DDR4_CH1_DQ48: JCPU1.AM10 (DDR1_DQ_48/DDR1_DQ_48); also elsewhere on the board
DDR4_CH1_DQ49: JCPU1.AL10 (DDR1_DQ_49/DDR1_DQ_49); also elsewhere on the board
DDR4_CH1_DQ50: JCPU1.AM7 (DDR1_DQ_50/DDR1_DQ_50); also elsewhere on the board
DDR4_CH1_DQ51: JCPU1.AL7 (DDR1_DQ_51/DDR1_DQ_51); also elsewhere on the board
DDR4_CH1_DQ52: JCPU1.AM9 (DDR1_DQ_52/DDR1_DQ_52); also elsewhere on the board
DDR4_CH1_DQ53: JCPU1.AL9 (DDR1_DQ_53/DDR1_DQ_53); also elsewhere on the board
DDR4_CH1_DQ54: JCPU1.AM6 (DDR1_DQ_54/DDR1_DQ_54); also elsewhere on the board
DDR4_CH1_DQ55: JCPU1.AL6 (DDR1_DQ_55/DDR1_DQ_55); also elsewhere on the board
DDR4_CH1_DQ56: JCPU1.AJ6 (DDR1_DQ_56/DDR1_DQ_56); also elsewhere on the board
DDR4_CH1_DQ57: JCPU1.AJ7 (DDR1_DQ_57/DDR1_DQ_57); also elsewhere on the board
DDR4_CH1_DQ58: JCPU1.AE6 (DDR1_DQ_58/DDR1_DQ_58); also elsewhere on the board
DDR4_CH1_DQ59: JCPU1.AF7 (DDR1_DQ_59/DDR1_DQ_59); also elsewhere on the board
DDR4_CH1_DQ60: JCPU1.AH7 (DDR1_DQ_60/DDR1_DQ_60); also elsewhere on the board
DDR4_CH1_DQ61: JCPU1.AH6 (DDR1_DQ_61/DDR1_DQ_61); also elsewhere on the board
DDR4_CH1_DQ62: JCPU1.AE7 (DDR1_DQ_62/DDR1_DQ_62); also elsewhere on the board
DDR4_CH1_DQ63: JCPU1.AF6 (DDR1_DQ_63/DDR1_DQ_63); also elsewhere on the board
DDR4_CH1_DQS0+: JCPU1.AF35 (DDR1_DQSP_0/DDR0_DQSP_2); also elsewhere on the board
DDR4_CH1_DQS0-: JCPU1.AF34 (DDR1_DQSN_0/DDR0_DQSN_2); also elsewhere on the board
DDR4_CH1_DQS1+: JCPU1.AL33 (DDR1_DQSP_1/DDR0_DQSP_3); also elsewhere on the board
DDR4_CH1_DQS1-: JCPU1.AK33 (DDR1_DQSN_1/DDR0_DQSN_3); also elsewhere on the board
DDR4_CH1_DQS2+: JCPU1.AP33 (DDR1_DQSP_2/DDR0_DQSP_6); also elsewhere on the board
DDR4_CH1_DQS2-: JCPU1.AN33 (DDR1_DQSN_2/DDR0_DQSN_6); also elsewhere on the board
DDR4_CH1_DQS3+: JCPU1.AN28 (DDR1_DQSP_3/DDR0_DQSP_7); also elsewhere on the board
DDR4_CH1_DQS3-: JCPU1.AN29 (DDR1_DQSN_3/DDR0_DQSN_7); also elsewhere on the board
DDR4_CH1_DQS4+: JCPU1.AN12 (DDR1_DQSP_4/DDR1_DQSP_2); also elsewhere on the board
DDR4_CH1_DQS4-: JCPU1.AN13 (DDR1_DQSN_4/DDR1_DQSN_2); also elsewhere on the board
DDR4_CH1_DQS5+: JCPU1.AP8 (DDR1_DQSP_5/DDR1_DQSP_3); also elsewhere on the board
DDR4_CH1_DQS5-: JCPU1.AR8 (DDR1_DQSN_5/DDR1_DQSN_3); also elsewhere on the board
DDR4_CH1_DQS6+: JCPU1.AL8 (DDR1_DQSP_6/DDR1_DQSP_6); also elsewhere on the board
DDR4_CH1_DQS6-: JCPU1.AM8 (DDR1_DQSN_6/DDR1_DQSN_6); also elsewhere on the board
DDR4_CH1_DQS7+: JCPU1.AG7 (DDR1_DQSP_7/DDR1_DQSP_7); also elsewhere on the board
DDR4_CH1_DQS7-: JCPU1.AG6 (DDR1_DQSN_7/DDR1_DQSN_7); also elsewhere on the board
DDR4_CH1_DQS8+: JCPU1.AN25 (DDR1_DQSP_8/DDR1_DQSP_8); also elsewhere on the board
DDR4_CH1_DQS8-: JCPU1.AN26 (DDR1_DQSN_8/DDR1_DQSN_8); also elsewhere on the board
DDR4_CH1_ECC0: JCPU1.AR25 (DDR1_ECC_0); also elsewhere on the board
DDR4_CH1_ECC1: JCPU1.AR26 (DDR1_ECC_1); also elsewhere on the board
DDR4_CH1_ECC2: JCPU1.AM26 (DDR1_ECC_2); also elsewhere on the board
DDR4_CH1_ECC3: JCPU1.AM25 (DDR1_ECC_3); also elsewhere on the board
DDR4_CH1_ECC4: JCPU1.AP26 (DDR1_ECC_4); also elsewhere on the board
DDR4_CH1_ECC5: JCPU1.AP25 (DDR1_ECC_5); also elsewhere on the board
DDR4_CH1_ECC6: JCPU1.AL25 (DDR1_ECC_6); also elsewhere on the board
DDR4_CH1_ECC7: JCPU1.AL26 (DDR1_ECC_7); also elsewhere on the board
DDR4_CH1_ODT0: JCPU1.AM16 (DDR1_ODT_0); also elsewhere on the board
DDR4_CH1_ODT1: JCPU1.AL16 (DDR1_ODT_1); also elsewhere on the board
DDR4_CH1_Parity: JCPU1.AL20 (DDR1_PAR); also elsewhere on the board

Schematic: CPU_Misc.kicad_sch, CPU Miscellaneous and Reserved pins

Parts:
JCPU1: Intel 8th/9th Generation Coffee-Lake LGA1151 CPU; LGA-1151_L47.1-W42.5-P0.91_PE115127-4041-01H
R34: 20Ω; R_0402_1005Metric

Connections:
GND: JCPU1.AY3 (VSS_125), JCPU1.G8 (VSS_124); also elsewhere on the board
unnamed: JCPU1.B3 (PROC_TRIGOUT), R34.2
TRIG_CPU_TO_PCH: R34.1; also elsewhere on the board
TRIG_PCH_TO_CPU: JCPU1.D1 (PROC_TRIGIN); also elsewhere on the board

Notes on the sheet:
place the resistor physically close to the OUT pin on each end?

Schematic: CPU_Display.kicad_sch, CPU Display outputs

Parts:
JCPU1: Intel 8th/9th Generation Coffee-Lake LGA1151 CPU; LGA-1151_L47.1-W42.5-P0.91_PE115127-4041-01H
R11: 24.9Ω_1%; R_0402_1005Metric
TP1: eDP-pwm-but-from-CPU?; TestPoint_Pad_D2.0mm

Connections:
CPU_DisplayAudio_CLK: JCPU1.V3 (PROC_AUDIO_CLK); also elsewhere on the board
CPU_DisplayAudio_SDI: JCPU1.V2 (PROC_AUDIO_SDI); also elsewhere on the board
CPU_DisplayAudio_SDO: JCPU1.U1 (PROC_AUDIO_SDO); also elsewhere on the board
unnamed: JCPU1.M9 (DISP_RCOMP), R11.2
unnamed: JCPU1.D14 (EDP_DISP_UTIL), TP1.1
VCCIO: R11.1; also elsewhere on the board
iGPU_DDI1_AUX+: JCPU1.B13 (DDI1_AUXP); also elsewhere on the board
iGPU_DDI1_AUX-: JCPU1.C13 (DDI1_AUXN); also elsewhere on the board
iGPU_DDI1_TX0+: JCPU1.C21 (DDI1_TXP_0); also elsewhere on the board
iGPU_DDI1_TX0-: JCPU1.D21 (DDI1_TXN_0); also elsewhere on the board
iGPU_DDI1_TX1+: JCPU1.D22 (DDI1_TXP_1); also elsewhere on the board
iGPU_DDI1_TX1-: JCPU1.E22 (DDI1_TXN_1); also elsewhere on the board
iGPU_DDI1_TX2+: JCPU1.B23 (DDI1_TXP_2); also elsewhere on the board
iGPU_DDI1_TX2-: JCPU1.A23 (DDI1_TXN_2); also elsewhere on the board
iGPU_DDI1_TX3+: JCPU1.C23 (DDI1_TXP_3); also elsewhere on the board
iGPU_DDI1_TX3-: JCPU1.D23 (DDI1_TXN_3); also elsewhere on the board
iGPU_DDI2_AUX+: JCPU1.A12 (DDI2_AUXP)
iGPU_DDI2_AUX-: JCPU1.B12 (DDI2_AUXN)
iGPU_DDI2_TX0+: JCPU1.B18 (DDI2_TXP_0); also elsewhere on the board
iGPU_DDI2_TX0-: JCPU1.A18 (DDI2_TXN_0); also elsewhere on the board
iGPU_DDI2_TX1+: JCPU1.D18 (DDI2_TXP_1); also elsewhere on the board
iGPU_DDI2_TX1-: JCPU1.E18 (DDI2_TXN_1); also elsewhere on the board
iGPU_DDI2_TX2+: JCPU1.C19 (DDI2_TXP_2); also elsewhere on the board
iGPU_DDI2_TX2-: JCPU1.D19 (DDI2_TXN_2); also elsewhere on the board
iGPU_DDI2_TX3+: JCPU1.D20 (DDI2_TXP_3); also elsewhere on the board
iGPU_DDI2_TX3-: JCPU1.E20 (DDI2_TXN_3); also elsewhere on the board
iGPU_DDI3_AUX+: JCPU1.B11 (DDI3_AUXP)
iGPU_DDI3_AUX-: JCPU1.C11 (DDI3_AUXN)
iGPU_DDI3_TX0+: JCPU1.B14 (DDI3_TXP_0); also elsewhere on the board
iGPU_DDI3_TX0-: JCPU1.A14 (DDI3_TXN_0); also elsewhere on the board
iGPU_DDI3_TX1+: JCPU1.C15 (DDI3_TXP_1); also elsewhere on the board
iGPU_DDI3_TX1-: JCPU1.B15 (DDI3_TXN_1); also elsewhere on the board
iGPU_DDI3_TX2+: JCPU1.B16 (DDI3_TXP_2); also elsewhere on the board
iGPU_DDI3_TX2-: JCPU1.A16 (DDI3_TXN_2); also elsewhere on the board
iGPU_DDI3_TX3+: JCPU1.C17 (DDI3_TXP_3); also elsewhere on the board
iGPU_DDI3_TX3-: JCPU1.B17 (DDI3_TXN_3); also elsewhere on the board
iGPU_eDP_AUX+: JCPU1.D12 (EDP_AUXP); also elsewhere on the board
iGPU_eDP_AUX-: JCPU1.E12 (EDP_AUXN); also elsewhere on the board
iGPU_eDP_TX0+: JCPU1.E10 (EDP_TXP_0); also elsewhere on the board
iGPU_eDP_TX0-: JCPU1.D10 (EDP_TXN_0); also elsewhere on the board
iGPU_eDP_TX1+: JCPU1.D9 (EDP_TXP_1); also elsewhere on the board
iGPU_eDP_TX1-: JCPU1.C9 (EDP_TXN_1); also elsewhere on the board
iGPU_eDP_TX2+: JCPU1.H10 (EDP_TXP_2); also elsewhere on the board
iGPU_eDP_TX2-: JCPU1.G10 (EDP_TXN_2); also elsewhere on the board
iGPU_eDP_TX3+: JCPU1.G9 (EDP_TXP_3); also elsewhere on the board
iGPU_eDP_TX3-: JCPU1.F9 (EDP_TXN_3); also elsewhere on the board

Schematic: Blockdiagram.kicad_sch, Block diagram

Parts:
H1: ATX_A; MountingHole_4.3mm_M4_Pad_Via
H2: ATX_C; MountingHole_4.3mm_M4_Pad_Via
H3: ATX_F; MountingHole_4.3mm_M4_Pad_Via
H4: ATX_G; MountingHole_4.3mm_M4_Pad_Via
H5: ATX_H; MountingHole_4.3mm_M4_Pad_Via
H6: ATX_J; MountingHole_4.3mm_M4_Pad_Via
H7: ATX_K; MountingHole_4.3mm_M4_Pad_Via; not fitted
H8: ATX_L; MountingHole_4.3mm_M4_Pad_Via; not fitted
H9: ATX_M; MountingHole_4.3mm_M4_Pad_Via; not fitted
H10: mATX_B; MountingHole_4.3mm_M4_Pad_Via
H11: mATX_R; MountingHole_4.3mm_M4_Pad_Via
H12: mATX_S; MountingHole_4.3mm_M4_Pad_Via

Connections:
GND: H1.1, H2.1, H3.1, H4.1, H5.1, H6.1, H7.1, H8.1, H9.1, H10.1, H11.1, H12.1; also elsewhere on the board

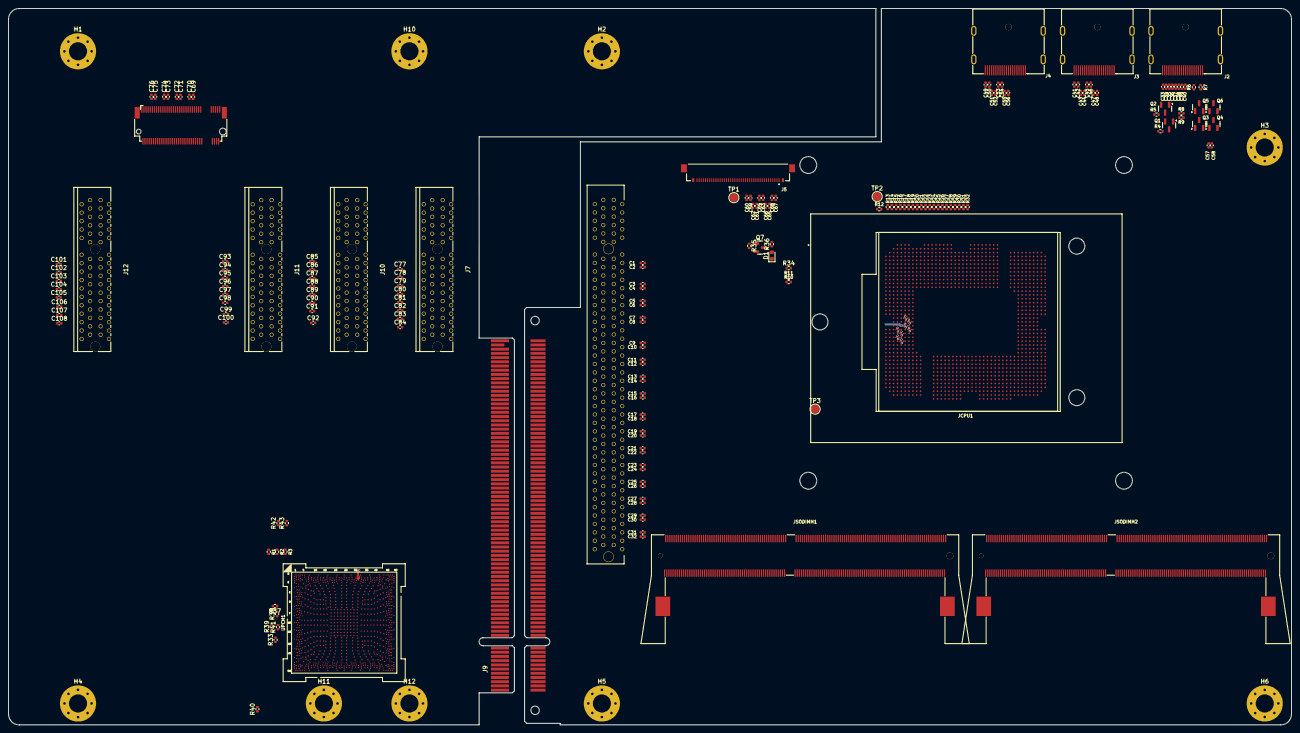
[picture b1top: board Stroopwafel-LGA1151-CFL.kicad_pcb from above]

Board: 2 copper layers, 304.8 x 170.2 mm, 187 parts (1 on the bottom side), 683 nets.
